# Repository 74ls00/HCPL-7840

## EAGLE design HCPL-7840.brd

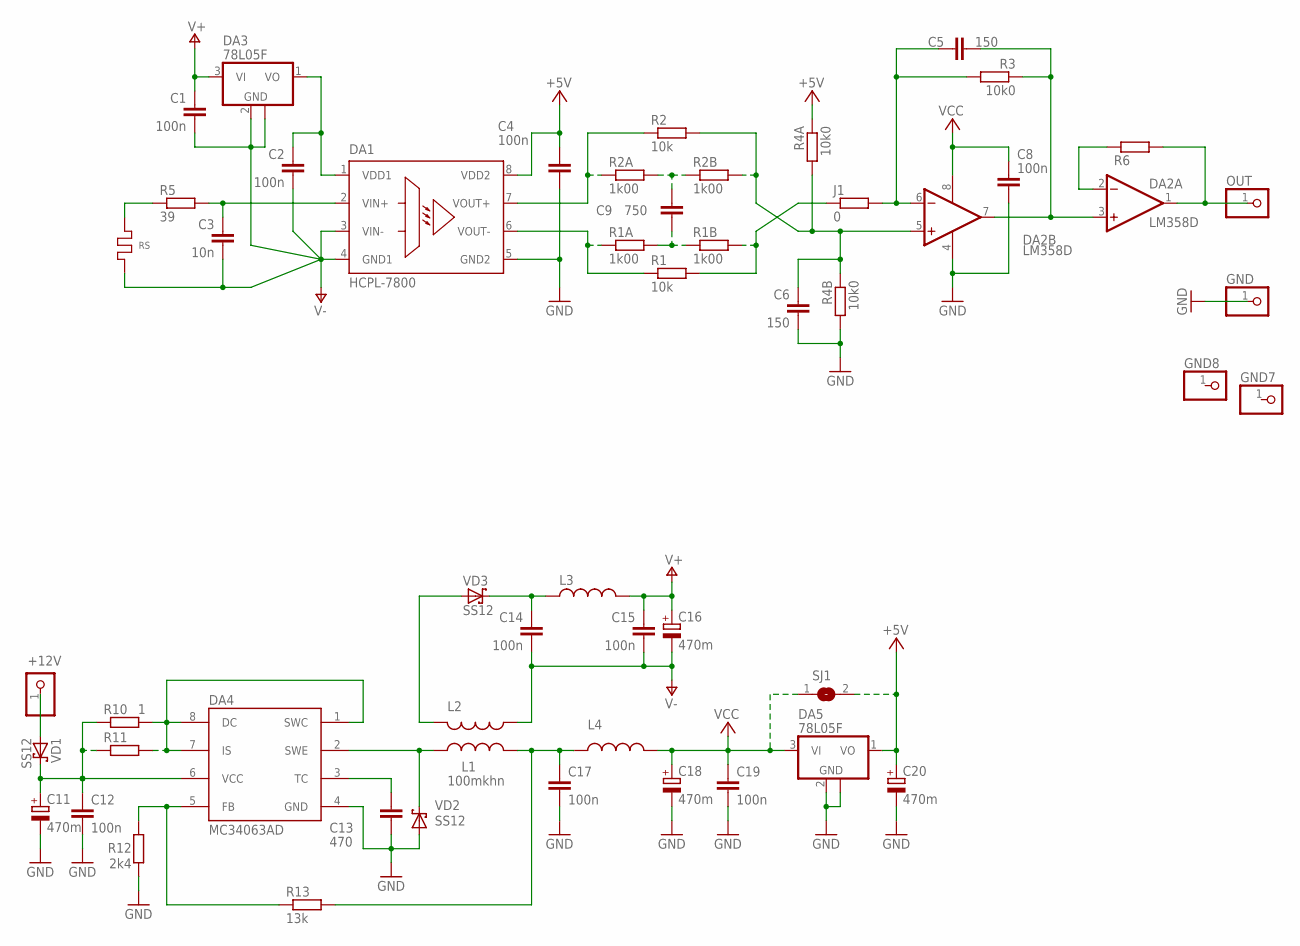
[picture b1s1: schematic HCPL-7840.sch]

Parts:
+12V: PINHD-1X1; 1X01
C1, C12, C14, C15, C17, C19: 100n; C0805
C2, C4, C8: 100n; C075-032X103
C3: 10n; C0805
C5, C6: 150; C0805
C9: 750; C0805
C11, C16, C18, C20: 470m; E2,5-5
C13: 470; C0805
DA1: HCPL-7800; DIL08
DA2: LM358D; SO08
DA3, DA5: 78L05F; SOT89
DA4: MC34063AD; SOIC8
GND, GND7, GND8: PINHD-1X1; 1X01
J1: 0; R1206W
L1: 100mkhn; LAN02KR
L2: L-USLAN02KR; LAN02KR
L3: L0204/7; 0204/7
L4: L-US0204/7; 0204/7
OUT: PINHD-1X1; 1X01
R1, R2: 10k; M0805
R1A, R1B, R2A, R2B: 1k00; M0805
R3, R4A, R4B: 10k0; M0805
R5: 39; M0805
R6: R-EU_M0805; M0805
R10: 1; M1206
R11: R-EU_M1206; M1206
R12: 2k4; M0805
R13: 13k; 0207/10
RS: R; 75ШС
SJ1: SJ
VD1, VD2, VD3: SS12; SMB

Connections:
+5V: C4.1, C20.+, DA1.8 (VDD2), DA5.1 (VO), R4A.1, SJ1.2
GND: C4.2, C6.2, C8.2, C11.-, C12.2, C13.2, C17.2, C18.-, C19.2, C20.-, DA1.5 (GND2), DA2.4 (V-), DA4.4 (GND), DA5.2 (GND), DA5.2@1 (GND), GND.1, R4B.2, R12.1, VD2.A
unnamed: C3.1, DA1.2 (VIN+), R5.2
unnamed: C2.1, DA1.1 (VDD1), DA3.1 (VO)
unnamed: C9.2, R1A.2, R1B.1
unnamed: C9.1, R2A.2, R2B.1
unnamed: C5.2, DA2.3 (+IN), DA2.7 (OUT), R3.1
unnamed: DA1.7 (VOUT+), R2.1, R2A.1
unnamed: DA1.6 (VOUT-), R1.1, R1A.1
unnamed: C6.1, DA2.5 (+IN), R2.2, R2B.2, R4A.2, R4B.1
unnamed: C5.1, DA2.6 (-IN), J1.2, R3.2
unnamed: C11.+, C12.1, DA4.6 (VCC), R10.1, R11.1, VD1.C
unnamed: +12V.1, VD1.A
unnamed: C17.1, L1.2, L4.1, R13.2
unnamed: DA2.1 (OUT), OUT.1, R6.2
unnamed: DA2.2 (-IN), R6.1
unnamed: L2.1, VD3.A
unnamed: C14.1, L3.1, VD3.C
unnamed: DA4.5 (FB), R12.2, R13.1
unnamed: J1.1, R1.2, R1B.2
unnamed: DA4.1 (SWC), DA4.7 (IS), DA4.8 (DC), R10.2, R11.2
unnamed: DA4.2 (SWE), L1.1, VD2.C
unnamed: C13.1, DA4.3 (TC)
R_SENSE: R5.1, RS.P$2
V+: C1.1, C15.1, C16.+, DA3.3 (VI), L3.2
V-: C1.2, C2.2, C3.2, C14.2, C15.2, C16.-, DA1.3 (VIN-), DA1.4 (GND1), DA3.2 (GND), DA3.2@1 (GND), L2.2, RS.P$1
VCC: C8.1, C18.+, C19.1, DA2.8 (V+), DA5.3 (VI), L4.2, SJ1.1

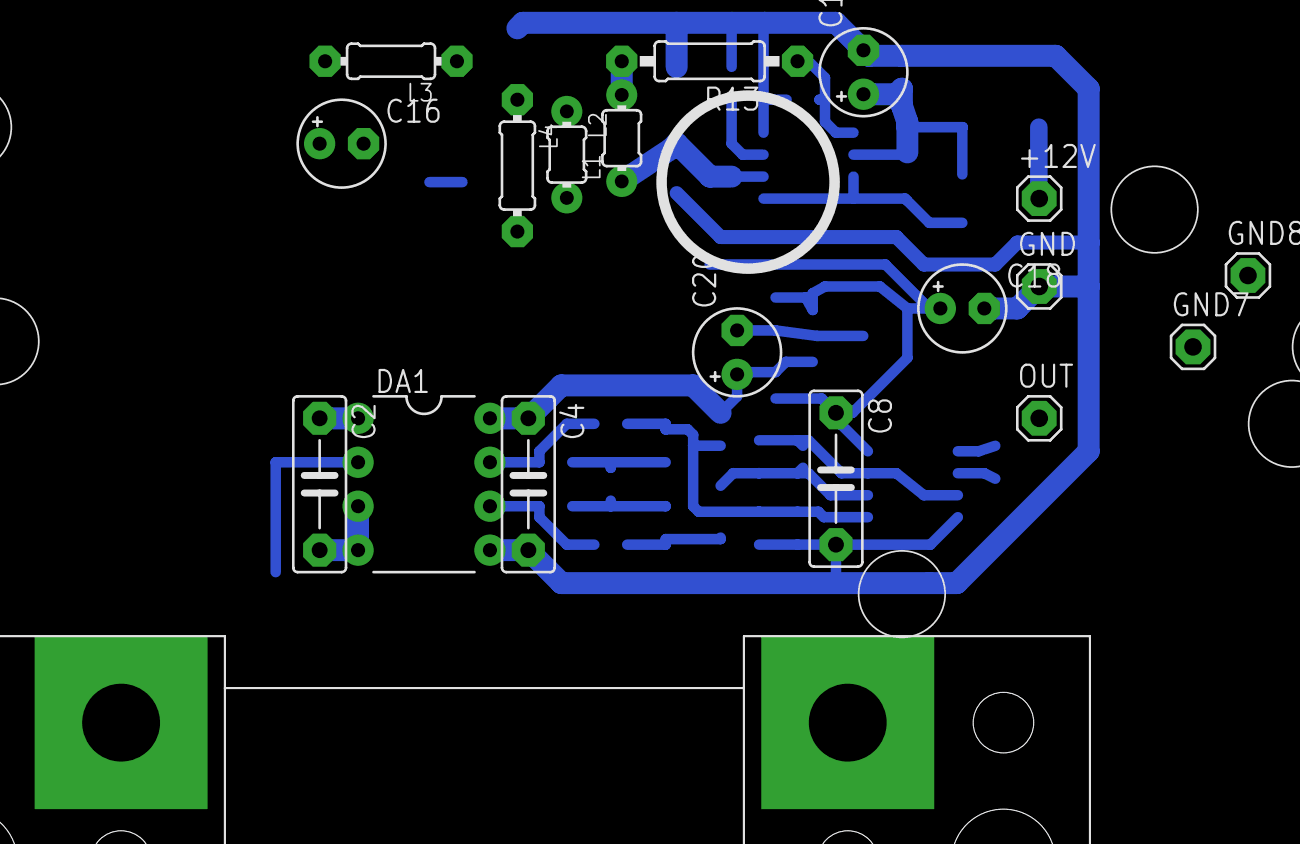
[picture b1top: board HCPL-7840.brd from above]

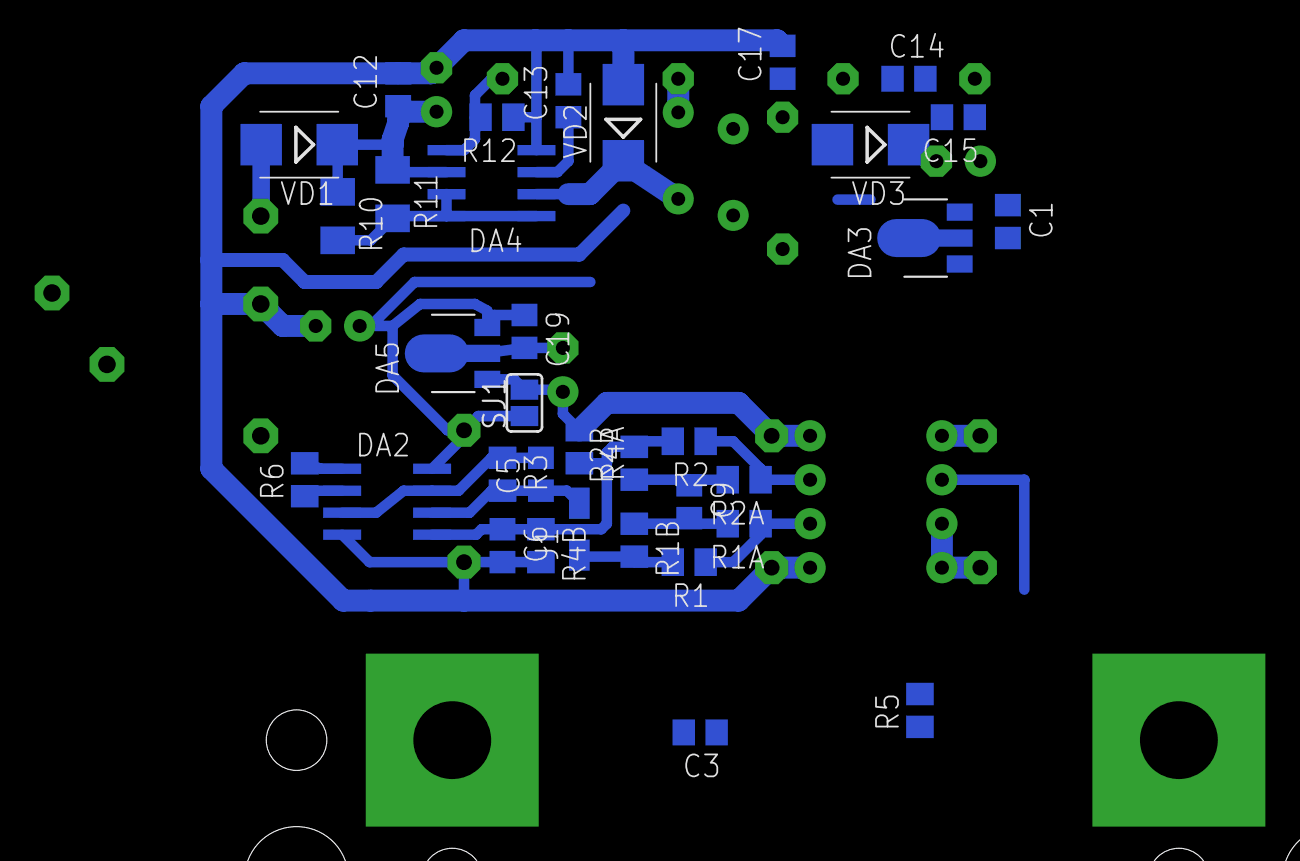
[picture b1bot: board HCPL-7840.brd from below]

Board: 2 copper layers, 53 parts (34 on the bottom side), 27 nets.
